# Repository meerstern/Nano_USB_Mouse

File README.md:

# Overview
  * This is a compact mouse equipped with 5 directional pad, size 14mm x 25mm.  
  * It features up, down, left, right, center buttons, and left/right click buttons.
  * The center button functions the same as the left mouse button.  
  * If you continue to tilt the knob, the speed changes in two stages.  
  * Suitable for small PCs and SBCs(Single Board Computers, like Raspberry Pi).   
  * It operates using standard drivers, without the need for a dedicated driver.   
  * You can change the mouse orientation according to the direction of the USB port.  

# Direction Setting
  * To configure the mouse orientation, insert the USB connector while holding the knob tilted in the desired "up" direction.   
  * The settings will be applied immediately.
  * If the settings are not applied, please perform the procedure again.  
  * The configuration data is automatically saved to flash memory.   
  * The orientation does not need to be set again for subsequent uses.  
  * The configuration data supports up to approximately 10,000 rewrite cycles.  
  * If you do not wish to change the orientation, connect this device to the USB port without pressing any buttons.  

# Target user
  * It is ideal for users who primarily use a keyboard and don't need a mouse, but still want to use one occasionally.  
  * It is ideal as a stopgap measure until the drivers for the mouse pad or touch panel are installed.
  * It is convenient to use in combination with a [Nano USB Scroller][1].  

# Note
  * Due to the use of up, down, left, and right buttons, diagonal movement is not possible.  
  * Please take care not to short-circuit or damage components on the back of the board.    
  * Please operate the knob gently. Operating it with excessive force may cause damage.  
  * PCB color, LED color, and other specifications are subject to change without notice.
    
## Appearance and examples

Combination use with the USB Nano Scroller 

[1]: https://github.com/meerstern/Nano_USB_Scroller/

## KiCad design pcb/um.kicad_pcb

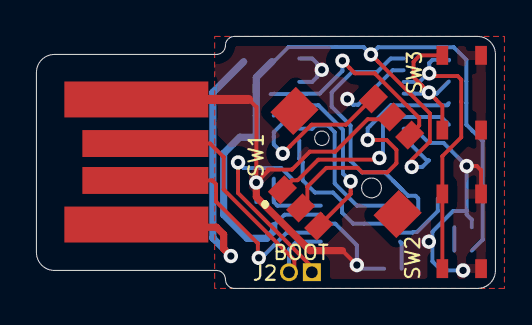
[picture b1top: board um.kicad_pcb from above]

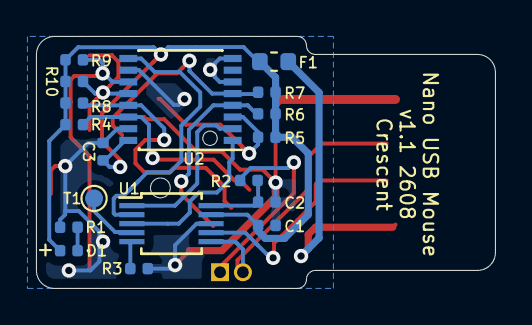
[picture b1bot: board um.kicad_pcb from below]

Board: 2 copper layers, 25.5 x 14.0 mm, 23 parts (18 on the bottom side), 20 nets.

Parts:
C1, C2, C3: 0.1u; C_0402_1005Metric
D1: GREEN; LED_0402_1005Metric
F1: 300mA; Fuse_0603_1608Metric
J1: USB_A; usbpcb
J2: BOOT; PinHeader_2x01_P1.27mm_Vertical
R1, R2, R3: 2.2k; R_0402_1005Metric
R4, R5, R6, R7, R8, R9, R10: 10k; R_0402_1005Metric
SW1: SKRHAAE010
SW2, SW3: SW_Push; SKRPACE010
T1: TEST; TestPoint_Pad_D1.0mm
U1: CH554E; MSOP-10_3x3mm_P0.5mm
U2: 74HC165; SSOP-16_4.4x5.2mm_P0.65mm

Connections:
+3V3: C2.1, R2.1, U1.10
+5V: C1.1, C3.1, D1.2, F1.2, R4.1, R5.1, R6.1, R7.1, R8.1, R9.1, R10.1, U1.9, U2.16
/DM: J1.2, U1.7
/DP: J1.3, J2.2, U1.6
/RST: R3.1, U1.5
/SCLK: U1.1, U2.2
/SCTR: U1.3, U2.1
/SOUT: U1.2, U2.9
/SW_A: R9.2, SW2.1, U2.11
/SW_B: R10.2, SW3.1, U2.12
/SW_C: R8.2, SW1.2, U2.13
/SW_D: R4.2, SW1.1, U2.14
/SW_E: R5.2, SW1.4, U2.3
/SW_F: R6.2, SW1.3, U2.4
/SW_G: R7.2, SW1.6, U2.5
GND: C1.2, C2.2, C3.2, J1.4, R1.2, R3.2, SW1.5, SW2.2, SW3.2, U1.8, U2.6, U2.8, U2.10, U2.15
unnamed: D1.1, R1.1
unnamed: F1.1, J1.1
unnamed: J2.1, R2.2
unnamed: T1.1, U1.4
